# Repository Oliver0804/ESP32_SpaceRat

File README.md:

# 此項目參考 
[ElectronicCats/SpaceRat](https://github.com/ElectronicCats/mpu6050)
# 項目內容

參考SpaceRat進行程序開發，於ESP32實現BLE HID為主要功能，
搭配EC12旋轉編碼器與MPU6500進行滑鼠控制。

### 準備材料

- ESP32
- MPU6500 (MPU6050)
- LCD Moudle SSD1308 I2C 0.96
- EC12/11
-
### 接線方式

### TODO List
- [ ] 加速動控制鼠標功能
- [ ] 低功耗機制 需搭配1.5V升壓3.3V
- [ ] OLED選單功能編寫
- [ ] 加速度校正機制

### library安裝
檔案放於Arduino library 

To install this library:

 - install it using the Arduino Library manager ("Sketch" -> "Include
   Library" -> "Manage Libraries..."), or
 - download a zipfile from github using the "Download ZIP" button and
   install it using the IDE ("Sketch" -> "Include Library" -> "Add .ZIP
   Library..."
 - clone this git repository into your sketchbook/libraries folder.

For more info, see https://www.arduino.cc/en/Guide/Libraries

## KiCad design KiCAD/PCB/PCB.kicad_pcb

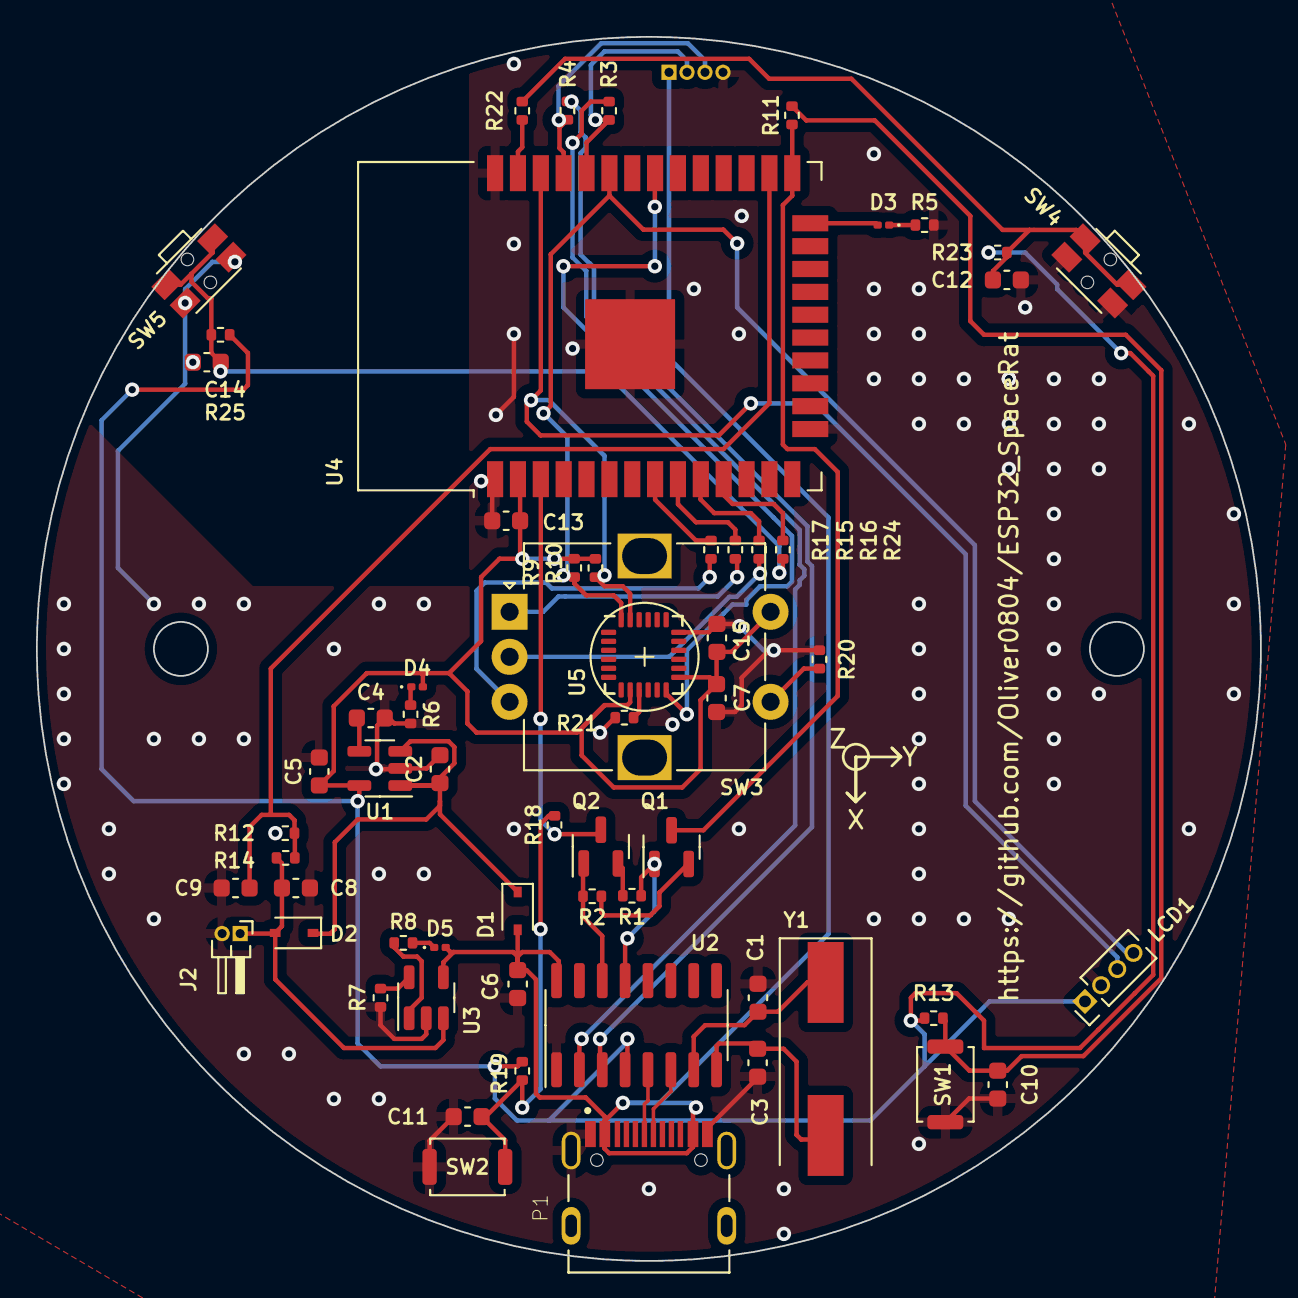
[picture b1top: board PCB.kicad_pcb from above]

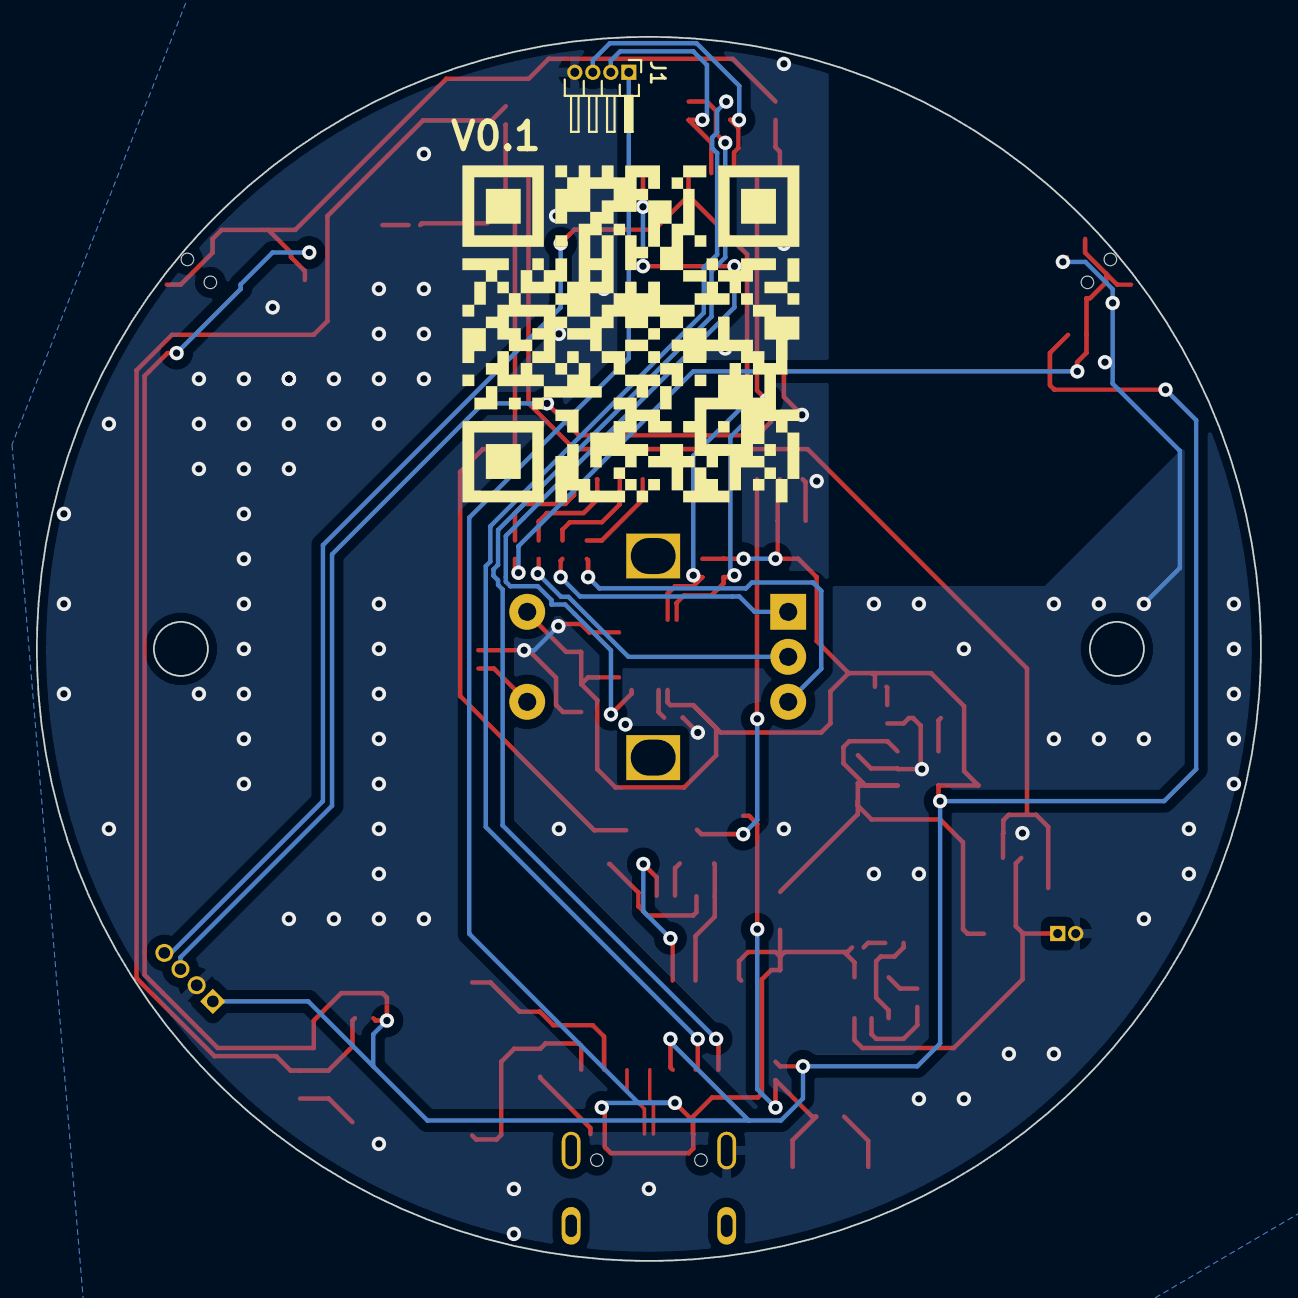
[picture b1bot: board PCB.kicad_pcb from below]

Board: 2 copper layers, 68.0 x 68.0 mm, 63 parts (2 on the bottom side), 44 nets.

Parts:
C1, C3: 22p; C_0603_1608Metric
C2, C6, C8: 4.7uF; C_0603_1608Metric
C4: 470pF; C_0603_1608Metric
C5: 2.2uF; C_0603_1608Metric
C7: 10uF; C_0603_1608Metric
C9: 100pF; C_0603_1608Metric
C10, C11, C12, C14, C15: 0.1uF; C_0603_1608Metric
C13: 10nF; C_0603_1608Metric
D1, D2: D; D_SOD-323
D3, D4, D5: LED; LED_0201_0603Metric
J1: Conn_01x04; PinHeader_1x04_P1.00mm_Horizontal
J2: Conn_01x02; PinHeader_1x02_P1.00mm_Horizontal
LCD1: Conn_01x04; PinHeader_1x04_P1.27mm_Vertical
P1: USB_C_Plug; HRI_TYPE_C
Q1, Q2: Q_NPN_EBC; SOT-23
R1, R2, R5, R6, R15, R16, R17: R; R_0402_1005Metric
R3, R9, R10, R23, R25: 4.7K; R_0402_1005Metric
R4: 1K; R_0402_1005Metric
R7: 2K; R_0402_1005Metric
R8, R11, R18: 470R; R_0402_1005Metric
R12: 1M; R_0402_1005Metric
R13, R19: 10K; R_0402_1005Metric
R14: 1MR; R_0402_1005Metric
R20: 10KR; R_0402_1005Metric
R21: NC; R_0402_1005Metric
R22, R24: 330R; R_0402_1005Metric
SW1, SW2: SW_Push; SW_Push_SPST_NO_Alps_SKRK
SW3: RotaryEncoder_Switch; RotaryEncoder_Alps_EC12E-Switch_Vertical_H20mm
SW4, SW5: SW_Push; SW_SPST_EVQP7C
U1: MIC5219-3.3YM5; SOT-23-5
U2: CH340G; SOIC-16_3.9x9.9mm_P1.27mm
U3: MCP73832-5-OT; SOT-23-5
U4: ESP32-WROOM-32D; ESP32-WROOM-32
U5: MPU-6050; InvenSense_QFN-24_4x4mm_P0.5mm
V0.1: LOGO
Y1: 12Mhz; Crystal_SMD_HC49-SD

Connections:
+3V3: C5.1, C7.1, C13.1, C15.1, D4.2 (A), LCD1.1, R9.1, R10.1, R13.1, R19.1, R23.1, R25.1, SW3.S1, U1.5 (OUT), U2.4 (V3), U4.2 (VDD), U5.8 (VDDIO), U5.13 (VDD)
+5V: C6.1, D1.2 (A), D5.2 (A), J1.1, P1.A4 (VBUS), P1.B4 (VBUS), U2.16 (VCC), U3.4 (VDD)
/ADC0: C9.1, R12.1, R14.1, U4.26 (IO4)
/BT1: R22.1, U4.37 (IO23)
/BT2: R24.1, U4.11 (IO26)
/DTR: Q1.1 (E), R1.1, U2.13 (~DTR)
/ENCODER_A: R15.1, U4.9 (IO33)
/ENCODER_B: R16.1, U4.10 (IO25)
/ENCODER_C: R17.1, U4.8 (IO32)
/ESP32_EN: Q2.3 (C), R18.1, U4.3 (EN)
/ESP32_IO0: Q1.3 (C), R11.1, U4.25 (IO0)
/ESP32_IO2: D3.2 (A), U4.24 (IO2)
/LCD_SCL: LCD1.3, R10.2, U4.36 (IO22), U5.23 (SCL)
/LCD_SDA: LCD1.4, R9.2, U4.33 (IO21), U5.24 (SDA)
/Li_BAT: C8.1, D2.2 (A), J2.1, R14.2, U3.3 (VBAT)
/MPU_INT: U4.31 (IO19), U5.12 (INT)
/RTS: Q2.1 (E), R2.2, U2.14 (~RTS)
/UART_RX: J1.2, R3.2, U4.34 (RXD0/IO3)
/UART_TX: J1.3, R4.2, U4.35 (TXD0/IO1)
/USB_D+: P1.A6 (D+), U2.5 (UD+)
/USB_D-: P1.A7 (D-), U2.6 (UD-)
GND: C1.2, C2.2, C3.2, C4.2, C5.2, C6.2, C7.2, C8.2, C9.2, C10.1, C11.1, C12.1, C13.2, C14.1, C15.2, J1.4, J2.2, LCD1.2, P1.A1 (GND), P1.B1 (GND), P1.S1 (SHIELD), R5.2, R6.2, R7.2, R12.2, R20.2, R21.2, SW1.1, SW2.1, SW4.1, SW5.1, U1.2 (GND), U2.1 (GND), U3.2 (VSS), U4.1 (GND), U4.15 (GND), U4.38 (GND), U4.39 (GND), U5.18 (GND)
unnamed: C1.1, U2.7 (XI), Y1.1
unnamed: C2.1, D1.1 (K), D2.1 (K), U1.1 (IN), U1.3 (EN)
unnamed: C3.1, U2.8 (XO), Y1.2
unnamed: C4.1, U1.4 (BP)
unnamed: C10.2, R11.2, R13.2, SW1.2
unnamed: C11.2, R18.2, R19.2, SW2.2
unnamed: C12.2, R22.2, R23.2, SW4.2
unnamed: C14.2, R24.2, R25.2, SW5.2
unnamed: D3.1 (K), R5.1
unnamed: D4.1 (K), R6.1
unnamed: D5.1 (K), R8.2
unnamed: Q1.2 (B), R2.1
unnamed: Q2.2 (B), R1.2
unnamed: R3.1, U2.2 (TXD)
unnamed: R4.1, U2.3 (RXD)
unnamed: R7.1, U3.5 (PROG)
unnamed: R8.1, U3.1 (STAT)
unnamed: R15.2, SW3.A
unnamed: R16.2, SW3.C
unnamed: R17.2, SW3.B
unnamed: R20.1, SW3.S2
unnamed: R21.1, U5.9 (AD0)

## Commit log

2022-01-26 MPU6500 LCD EC12 BLE HID編碼器以整合待測試
2022-01-27 提升代碼可讀性
2022-01-27 整理目錄結構
2022-01-27 add readme and 接線圖
2022-01-27 優化個項目基礎功能
2022-01-27 加入i2c scanner工具
2022-01-28 更新Ble HID庫 加入免彈簧機構方式
2022-03-02 添加蘑菇頭FreeCAD檔案
2022-03-03 fixed error size
2022-03-03 update 外殼彈簧
2022-03-03 1 kicad初步繪製 2 freecad導入電路板尺寸 3 增加datasheet資料夾
2022-03-08 原理圖第一版完成
2022-03-12 完成佈件
2022-03-18 完成佈線
2022-03-24 更新第二版原理圖
